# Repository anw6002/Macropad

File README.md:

# Custom Hot-Swappable Macropad for League of Legends

## Overview

This project implements a custom USB macropad using the Raspberry Pi Pico.
The macropad is designed for League of Legends, providing dedicated QWER ability
keys, DF keys, and rotary encoder for volume controls. The firmware is written in C using the
Raspberry Pi Pico SDK, and the final hardware is designed in KiCad and
manufactured as a custom PCB.

There is a planned joystick expansion for character movement using League's new WASD support.
Up to 20 additional keys will be included in the expansion. 

## Hardware Design

The PCB is designed in KiCad for a Raspberry Pi Pico-based USB HID macropad (also compatible with the Raspberry Pi Pico 2). The board is intended to support six mechanical keyboard switches, with hot-swap sockets for easier switch replacement. The PCB will connect each key to a dedicated GPIO pin, with the switches sharing a common ground. The PCB design will accommodate a rotary encoder with push button for volume-control functionality.

### PCB Specifications

- **EDA software:** KiCad 10
- **Microcontroller:** Raspberry Pi Pico
- **Input switches:** 6 mechanical keyboard switches
- **Switch mounting:** Kailh CPG151101S11 hot-swap sockets
- **PCB layout:** Custom-designed PCB with a 4-key top row and 2 additional keys on the right side
- **Enclosure:** Custom 3D-printed case (planned)
- **Connectivity:** USB through the Pico's onboard connector
- **Firmware:** C using the Raspberry Pi Pico SDK and TinyUSB

### Hardware Components

| Component | Purpose | 
|---|---|
| Raspberry Pi Pico | Microcontroller and USB HID interface |
| Kailh CPG151101S11 hot-swap sockets | Allow switches to be replaced without desoldering |
| MX Mechanical keyboard switches | Physical key inputs |
| Custom PCB | Mounts switches and microcontroller connections |
| Header pins / sockets | Connects the Pico to the PCB |
| 3D-printed enclosure | Houses and protects the assembled macropad |
| Rotary encoder | volume control knob |

### GPIO Mapping

| Key | Pico GPIO | Physical Pin |
|---|---:|---:|
| Q | GP01 | 02 |
| W | GP05 | 07 |
| E | GP09 | 12 |
| R | GP15 | 20 |
| D | GP13 | 17 |
| F | GP14 | 19 |

The switches use a shared ground connection, with GPIO internal pull-ups intended to be enabled in firmware.

### PCB Development Roadmap

- [x] Create the initial schematic
- [x] Assign initial switch footprints
- [x] Import the schematic into the PCB editor
- [x] Finalize component placement and board outline
- [x] Verify switch socket and Pico header footprints against physical components
- [x] Route PCB traces
- [x] Run electrical and design-rule checks
- [x] Generate manufacturing files
- [x] Manufacture and assemble the PCB
- [ ] Design and print the enclosure
- [ ] Test the assembled macropad

*The PCB is a work in progress. Footprint compatibility, electrical connections, clearances, and manufacturing outputs must be verified before fabrication.*

## Project Roadmap

- [x] Prototype button circuit on a breadboard
- [x] Test each switch and verify wiring
- [x] Develop firmware for button detection and debouncing
- [x] Implement USB HID keyboard functionality
- [ ] Add macro support
- [ ] Add rotary encoder functionality
- [x] Design the schematic in KiCad
- [x] Route and manufacture the PCB
- [ ] Assemble and test the final board
- [ ] Design and print a case

## Technologies
- C
- CAD (3D Printed Case)
- Raspberry Pi Pico SDK
- TinyUSB
- KiCad
- Git
- VS Code

## Button Module Specifications

### Purpose

The button module provides an interface for initializing and scanning the macropad's pushbuttons. It abstracts the GPIO hardware and reports button press and release events.

### Functional Requirements
- Initialize all configured GPIO pins as digital inputs.
- Enable the Raspberry Pi Pico's internal pull-up resistors.
- Scan all buttons periodically.
- Detect button press events.
- Detect button release events.
- Generate exactly one press event for each physical press.
- Generate exactly one release event for each physical release.

### Assumptions
- Buttons are active-low.
- One side of every switch is connected to a GPIO pin.
- The opposite side is connected to ground.
- Internal pull-up resistors are enabled.
- buttons_scan() is called periodically from the main loop.

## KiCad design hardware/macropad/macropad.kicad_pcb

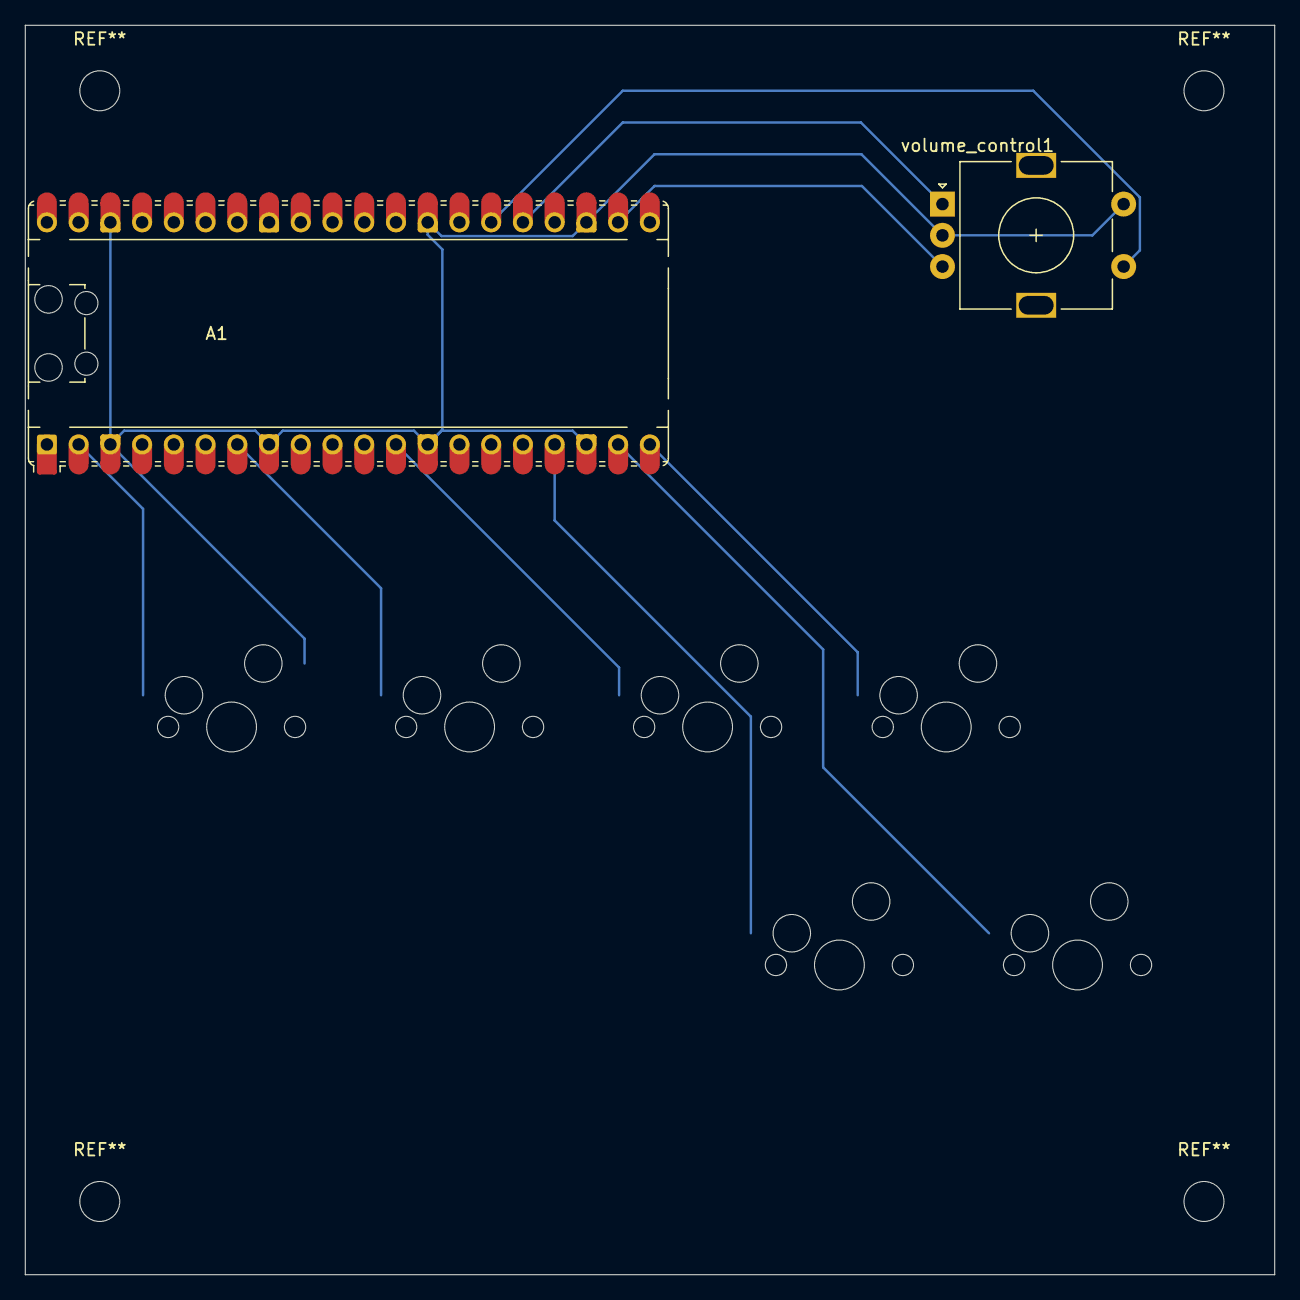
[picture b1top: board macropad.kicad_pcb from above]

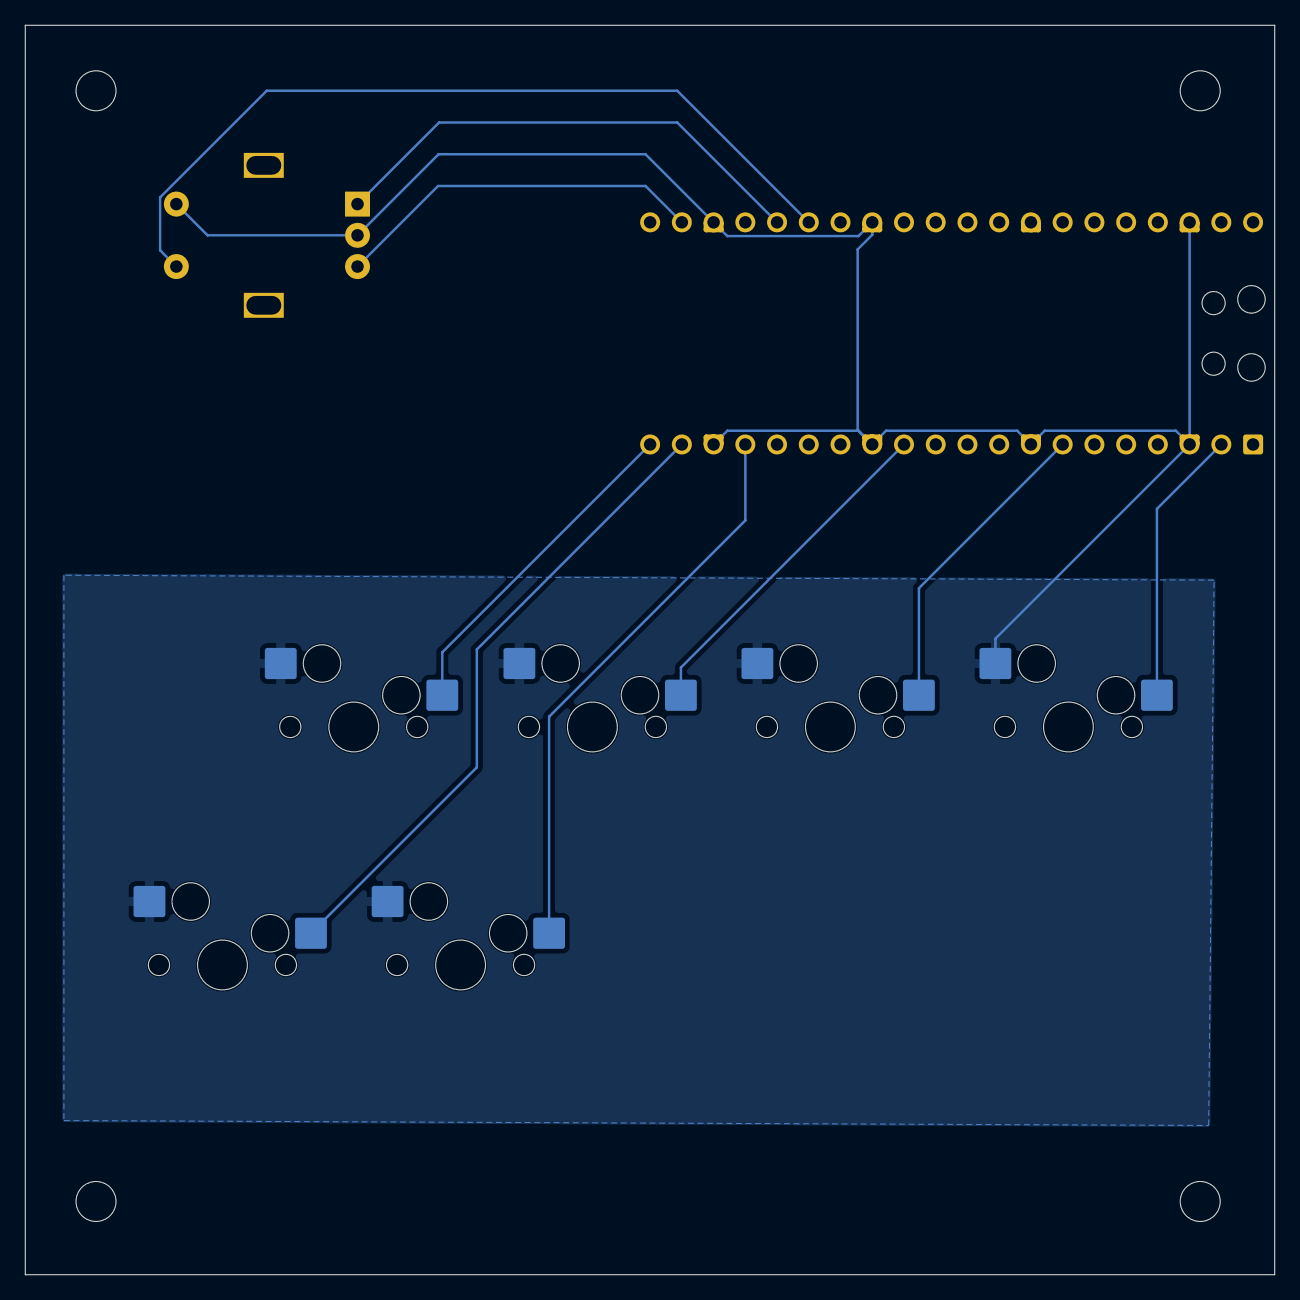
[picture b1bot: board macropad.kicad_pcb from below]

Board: 2 copper layers, 100.0 x 100.0 mm, 8 parts (6 on the bottom side), 8 nets.

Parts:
A1: RaspberryPi_Pico; RaspberryPi_Pico_Common_Unspecified
D1: SW_Push; MX-Hotswap-1U
E1: SW_Push; MX-Hotswap-1U
F1: SW_Push; MX-Hotswap-1U
Q1: SW_Push; MX-Hotswap-1U
R1: SW_Push; MX-Hotswap-1U
W1: SW_Push; MX-Hotswap-1U
volume_control1: RotaryEncoder_Switch; RotaryEncoder_Alps_EC11E-Switch_Vertical_H20mm

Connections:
GND: A1.3 (GND), A1.8 (GND), A1.13 (GND), A1.18 (GND), A1.23 (GND), A1.28 (GND), A1.38 (GND), D1.2, E1.2, F1.2, Q1.2 (2_2), R1.2, W1.2 (2_2), volume_control1.C, volume_control1.S2
unnamed: A1.12 (GPIO9), E1.1
unnamed: A1.17 (GPIO13), D1.1
unnamed: A1.19 (GPIO14), F1.1
unnamed: A1.20 (GPIO15), R1.1
unnamed: A1.22 (GPIO17), volume_control1.B
unnamed: A1.25 (GPIO19), volume_control1.A
unnamed: A1.26 (GPIO20), volume_control1.S1
